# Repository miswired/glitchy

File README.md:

# CircuitBreakerGadget

## Project Overview
Designed as an introduction into hardware hacking, the Glitchy can do power glitching to alter program execution and power analysis for extracting secrets from chips. 
See the [wiki](https://github.com/miswired/glitchy/wiki) for setup instructions and guides to performing the labs with the kit.

## Install
This project is hosted in two repos. The board firmware and PCB is hosted here. Please see the following instructions for setting up the build enviroment and programming. [Arduino-Setup](https://github.com/miswired/glitchy/wiki/Guide-%E2%80%90-Arduino-Setup)   

**The web gui has be substatually upgradded by Philip Kopyscinski!**  
See the following repo for the files you need to put on the SD card.  
https://github.com/pkopysci/miswired-glitchy-vue-app

## Comming Features
* Scripting power analysis attack
* Configure wifi from a config file on sd card isntead of having to reprogram

## Release Notes
### 2.0.0
#### New Features
* Completely new web GUI!!!
* Adjustability of glitching parameters from web interface

### 1.1.0
#### New Features
* None

#### Bug Fixes
* Fixed loading bug for the web interface

#### Backlog

* Add configuration of the glitching settings to the web interface instead of needing to reflash the chip
* Add wifi configuration to a config.ini file on the SD card instead of needing to reflash the chip

## Project Setup
Install Arduino IDE V1. Please see the following wiki for a setup guide. [Arduino-Setup](https://github.com/miswired/glitchy/wiki/Guide-%E2%80%90-Arduino-Setup)  

## Colaborators
**Miswired**  
https://github.com/miswired  
PCB Board and firmware  
  
**Philip J Kopyscinski**  
https://github.com/pkopysci  
Web GUI

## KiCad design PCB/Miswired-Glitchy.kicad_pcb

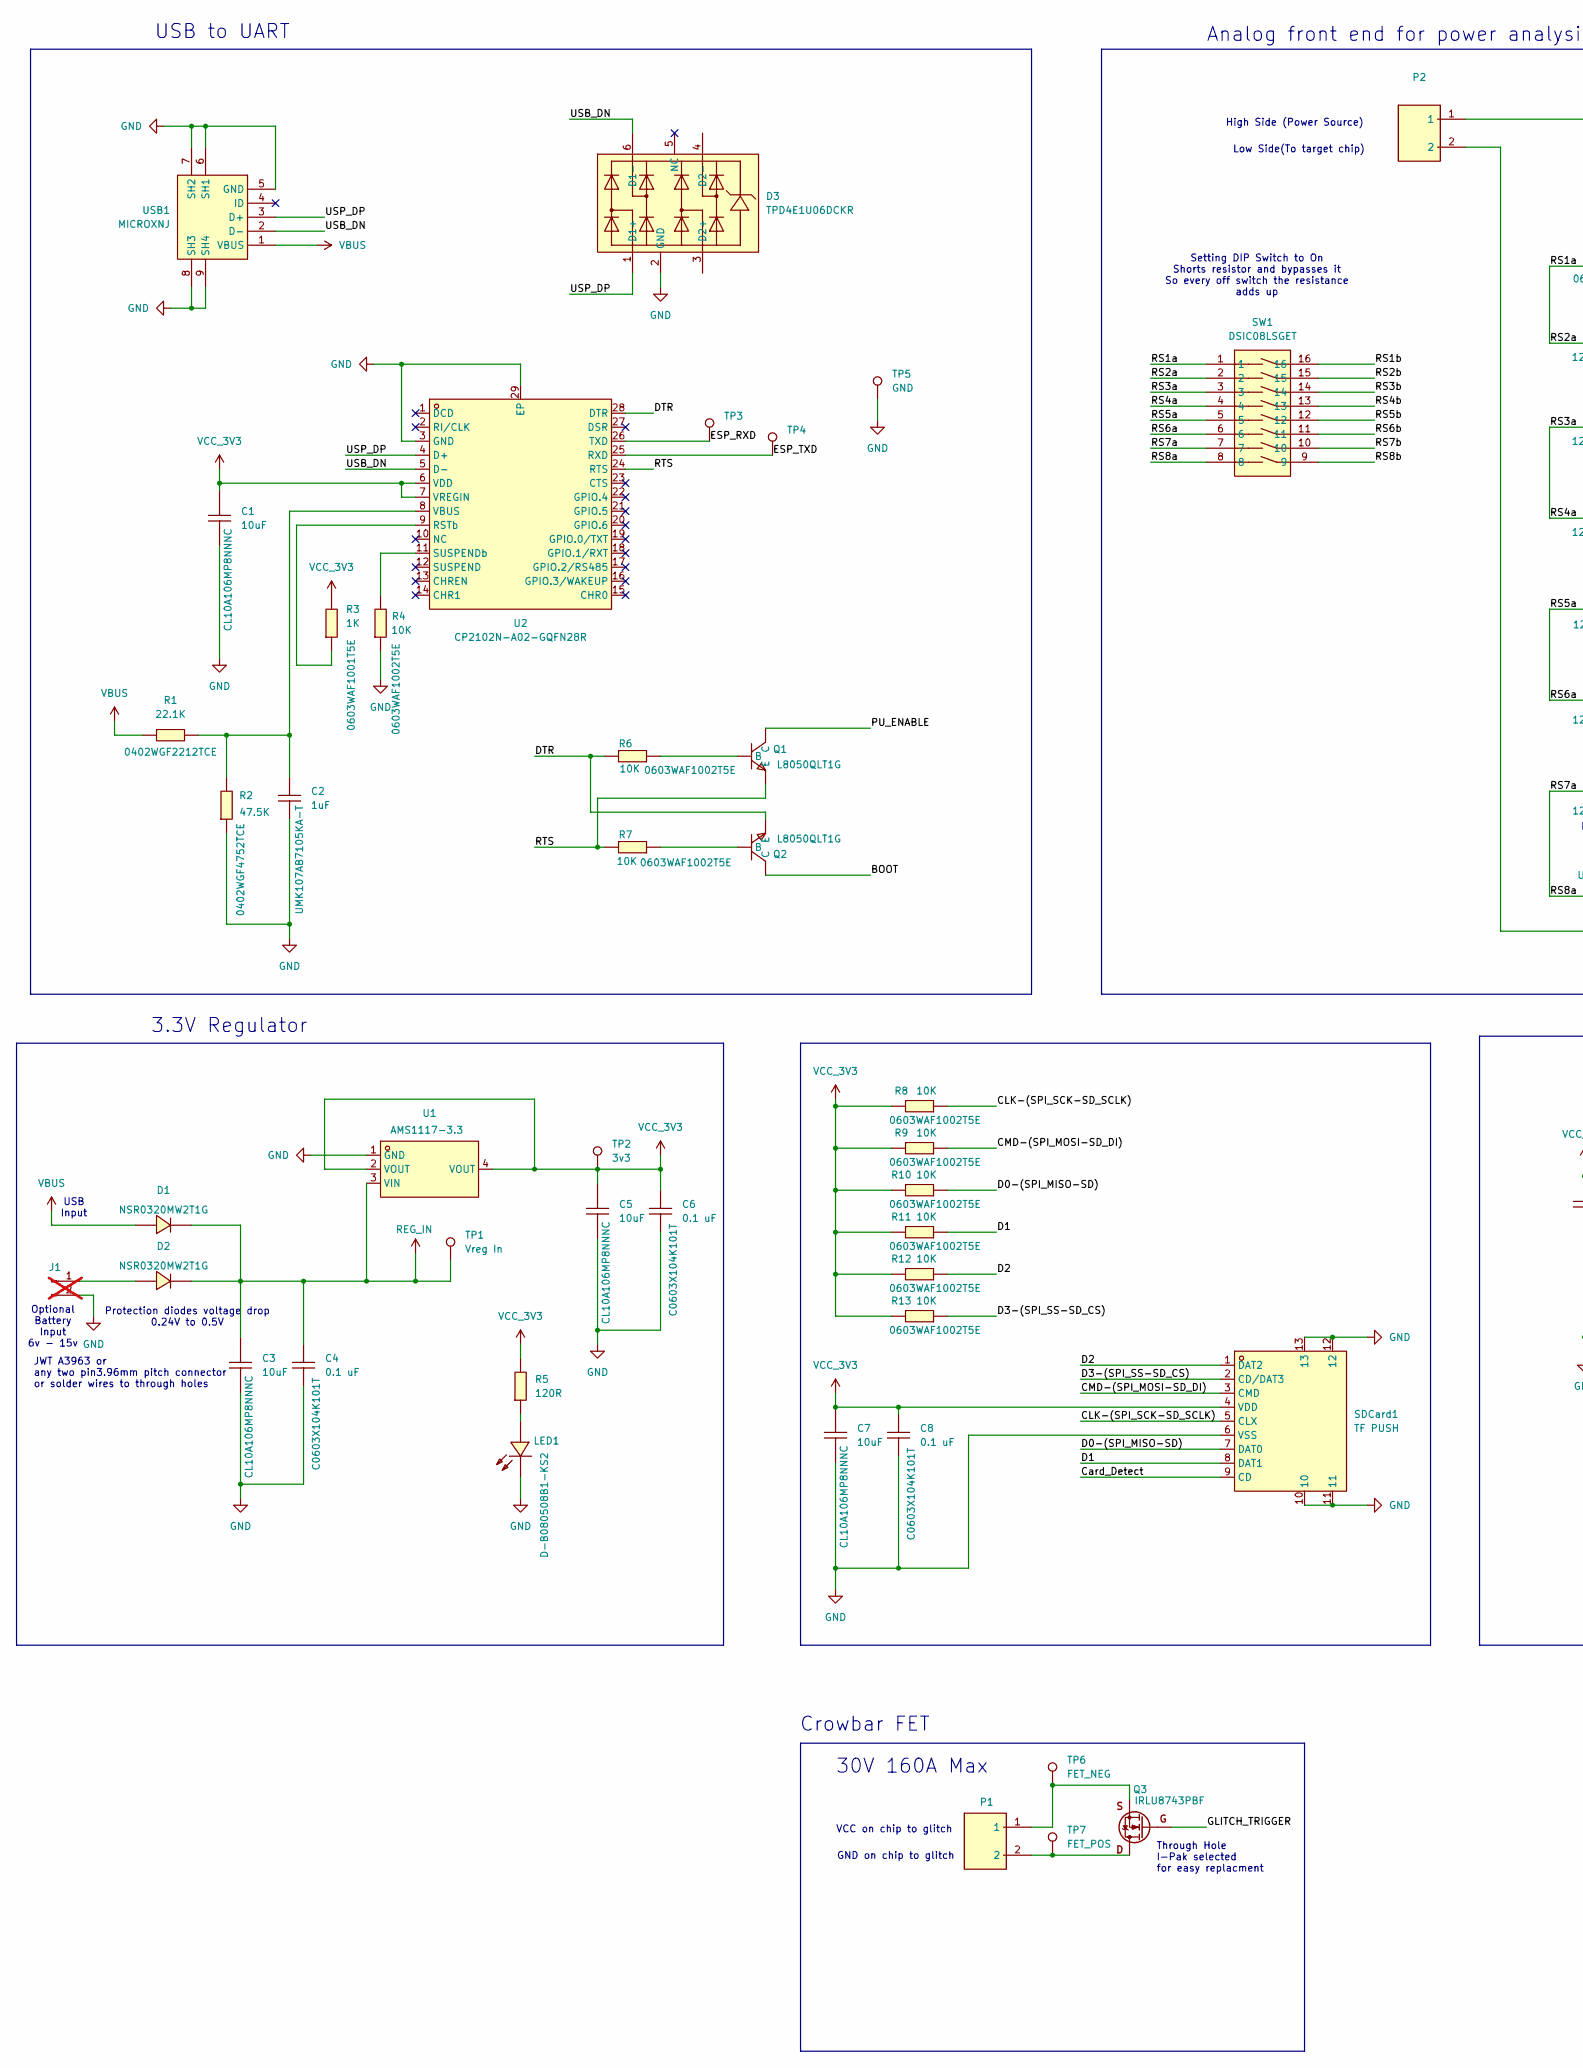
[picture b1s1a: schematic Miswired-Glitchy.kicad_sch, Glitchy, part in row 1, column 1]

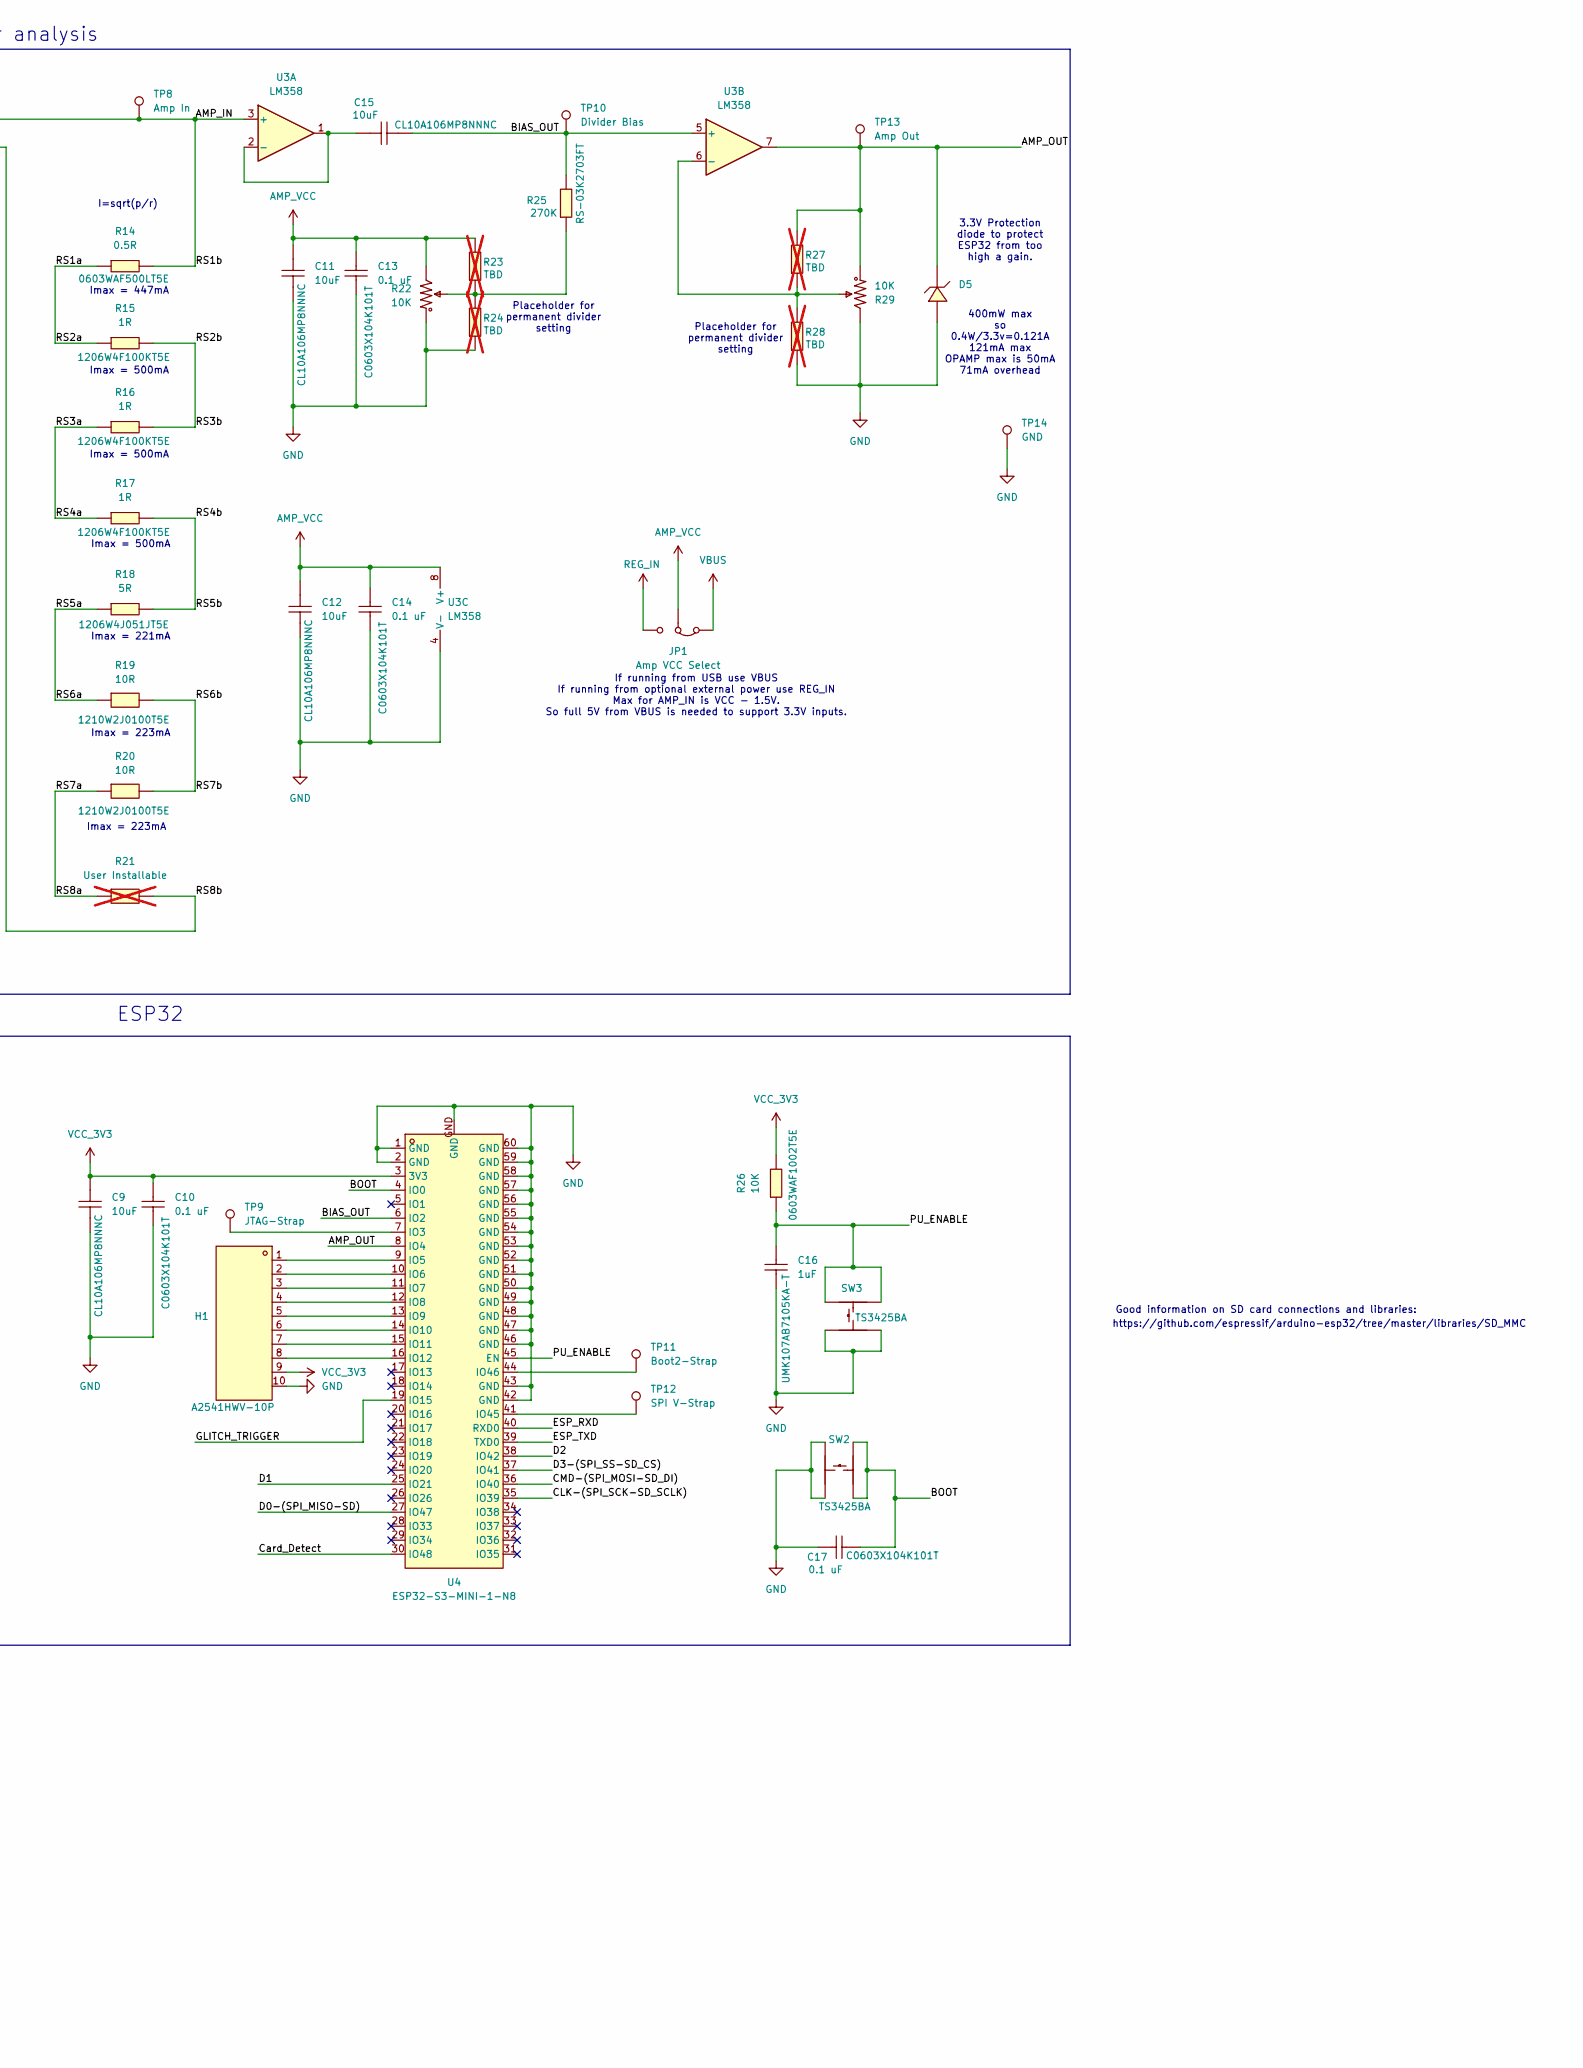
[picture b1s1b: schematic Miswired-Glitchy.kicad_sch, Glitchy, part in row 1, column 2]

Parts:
C1, C3, C5, C7, C9, C11, C12, C15: 10uF; C0603; MPN CL10A106MP8NNNC; LCSC Part C85713
C2, C16: 1uF; C0603; MPN UMK107AB7105KA-T; LCSC Part C105174
C4, C6, C8, C10, C13, C14, C17: 0.1 uF; C0603; MPN C0603X104K101T; LCSC Part C105907
D1, D2: SOD-323_L1.8-W1.3-LS2.5-RD; MPN NSR0320MW2T1G; LCSC Part C48192
D3: TPD4E1U06DCKR; SC-70-6_L2.2-W1.3-P0.65-LS2.1-BL; LCSC Part C194628
D5: PDZ3.3B,115; SOD-323_L1.7-W1.3-LS2.5-RD; MPN PDZ3.3B,115; LCSC Part C426855
H1: HDR-TH_10P-P2.54-V-F-1; MPN A2541HWV-10P; LCSC Part C225507
J1: Battery Placeholder; JWT_A3963_1x02_P3.96mm_Vertical; not fitted
JP1: Amp VCC Select; SolderJumper-3_P1.3mm_Bridged12_RoundedPad1.0x1.5mm_NumberL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
LED1: Blue; LED0805-RD; MPN D-B080508B1-KS2; LCSC Part C108412
P1, P2: CONN-TH_WJ126V-5.0-2P; MPN WJ126V-5.0-2P; LCSC Part C8404
Q1, Q2: SOT-23-3_L2.9-W1.3-P1.90-LS2.4-BR; MPN L8050QLT1G; LCSC Part C49581
Q3: IRLU8743PBF; TO-251-3_Vertical; MPN IRLU8743PBF
R1: 22.1K; R0402; MPN 0402WGF2212TCE; LCSC Part C43473
R2: 47.5K; R0402; MPN 0402WGF4752TCE; LCSC Part C25896
R3: 1K; R0603; MPN 0603WAF1001T5E; LCSC Part C21190
R4, R6, R7, R8, R9, R10, R11, R12, R13, R26: 10K; R0603; MPN 0603WAF1002T5E; LCSC Part C25804
R5: 120R; R0603; MPN 0603WAF1200T5E; LCSC Part C22787
R14: 0.5R; R0603; MPN 0603WAF500LT5E; LCSC Part C45312
R15, R16, R17: 1R; R1206; MPN 1206W4F100KT5E; LCSC Part C17928
R18: 5R; R1206; MPN 1206W4J051JT5E; LCSC Part C37912
R19, R20: 10R; R1210; MPN 1210W2J0100T5E; LCSC Part C473562
R21: User Installable; R_Box_L8.4mm_W2.5mm_P5.08mm; not fitted
R22, R29: 10K; RES-ADJ-TH_3P-L10.0-W10.0-P2.50-L; MPN 3296W-1-103; LCSC Part C118954
R23, R24, R27, R28: TBD; R0603; not fitted
R25: 270K; R0603; MPN RS-03K2703FT; LCSC Part C310276
SDCard1: TF PUSH; TF-SMD_TF-PUSH; LCSC Part C393941
SW1: DSIC08LSGET; SW-SMD_DSIC08LSGET; LCSC Part C54953
SW2, SW3: SW-SMD_4P-L4.2-W3.2-P2.15-LS4.6-1; MPN TS3425BA; LCSC Part C2681476
TP1: Vreg In; TestPoint_Pad_2.0x2.0mm
TP2: 3v3; TestPoint_Pad_2.0x2.0mm
TP3, TP4: TestPoint_Pad_2.0x2.0mm
TP5: GND; TestPoint_Pad_2.0x2.0mm
TP6: FET_NEG; TestPoint_THTPad_D2.0mm_Drill1.0mm
TP7: FET_POS; TestPoint_THTPad_D2.0mm_Drill1.0mm
TP8: Amp In; TestPoint_THTPad_D2.0mm_Drill1.0mm
TP9: JTAG-Strap; TestPoint_Pad_2.0x2.0mm
TP10: Divider Bias; TestPoint_THTPad_D2.0mm_Drill1.0mm
TP11: Boot2-Strap; TestPoint_Pad_2.0x2.0mm
TP12: SPI V-Strap; TestPoint_Pad_2.0x2.0mm
TP13: Amp Out; TestPoint_THTPad_D2.0mm_Drill1.0mm
TP14: GND; TestPoint_THTPad_D2.0mm_Drill1.0mm
U1: SOT-223-3_L6.5-W3.4-P2.30-LS7.0-BR; MPN AMS1117-3.3; LCSC Part C6186
U2: CP2102N-A02-GQFN28R; QFN-28_L5.0-W5.0-P0.50-TL-EP3.3; LCSC Part C964632
U3: LM358; SOP-8_L4.9-W3.9-P1.27-LS6.0-BL; MPN LM358DT; LCSC Part C9418
U4: ESP32-S3-MINI-1-N8; BULETM-SMD_ESP32-S3-MINI-1-N8; LCSC Part C2913206
USB1: MICROXNJ; MICRO-USB-SMD_MICROXNJ; LCSC Part C404969

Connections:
/AMP_IN: P2.1, R14.2, SW1.16, TP8.1, U3.3 (+)
/AMP_OUT: D5.1 (K), R27.2, R29.1, TP13.1, U3.7, U4.8 (IO4)
/BIAS_OUT: C15.2, R25.2, TP10.1, U3.5 (+), U4.6 (IO2)
/BOOT: C17.2, Q2.3 (C), SW2.1, SW2.2, U4.4 (IO0)
/CLK-(SPI_SCK-SD_SCLK): R8.1, SDCard1.5 (CLX), U4.35 (IO39)
/CMD-(SPI_MOSI-SD_DI): R9.1, SDCard1.3 (CMD), U4.36 (IO40)
/Card_Detect: SDCard1.9 (CD), U4.30 (IO48)
/D0-(SPI_MISO-SD): R10.1, SDCard1.7 (DAT0), U4.27 (IO47)
/D1: R11.1, SDCard1.8 (DAT1), U4.25 (IO21)
/D2: R12.1, SDCard1.1 (DAT2), U4.38 (IO42)
/D3-(SPI_SS-SD_CS): R13.1, SDCard1.2 (CD/DAT3), U4.37 (IO41)
/DTR: Q2.2 (E), R6.2, U2.28 (DTR)
/ESP_RXD: TP3.1, U2.26 (TXD), U4.40 (RXD0)
/ESP_TXD: TP4.1, U2.25 (RXD), U4.39 (TXD0)
/GLITCH_TRIGGER: Q3.1 (G), U4.19 (IO15)
/PU_ENABLE: C16.2, Q1.3 (C), R26.1, SW3.1, SW3.2, U4.45 (EN)
/RS1a: R14.1, R15.1, SW1.1, SW1.2
/RS2b: R15.2, R16.2, SW1.14, SW1.15
/RS3a: R16.1, R17.1, SW1.3, SW1.4
/RS4b: R17.2, R18.2, SW1.12, SW1.13
/RS5a: R18.1, R19.1, SW1.5, SW1.6
/RS6b: R19.2, R20.2, SW1.10, SW1.11
/RS7a: R20.1, R21.1, SW1.7, SW1.8
/RS8b: P2.2, R21.2, SW1.9
/RTS: Q1.2 (E), R7.2, U2.24 (RTS)
/USB_DN: D3.6 (D1-), U2.5 (D-), USB1.2 (D-)
/USP_DP: D3.1 (D1+), U2.4 (D+), USB1.3 (D+)
AMP_VCC: C11.1, C12.1, C13.2, C14.2, JP1.2 (C), R22.3, R23.2, U3.8 (V+)
GND: C1.2, C2.1, C3.2, C4.1, C5.2, C6.1, C7.2, C8.1, C9.2, C10.1, C11.2, C12.2, C13.1, C14.1, C16.1, C17.1, D3.2 (GND), D5.2 (A), H1.10, J1.2, LED1.1 (K), R2.1, R4.1, R22.1, R24.1, R28.1, R29.3, SDCard1.6 (VSS), SDCard1.10, SDCard1.11, SDCard1.12, SDCard1.13, SW2.3, SW2.4, SW3.3, SW3.4, TP5.1, TP14.1, U1.1 (GND), U2.3 (GND), U2.29 (EP), U3.4 (V-), U4.1 (GND), U4.2 (GND), U4.42 (GND), U4.43 (GND), U4.46 (GND), U4.47 (GND), U4.48 (GND), U4.49 (GND), U4.50 (GND), U4.51 (GND), U4.52 (GND), U4.53 (GND), U4.54 (GND), U4.55 (GND), U4.56 (GND), U4.57 (GND), U4.58 (GND), U4.59 (GND), U4.60 (GND), U4.GND, USB1.5 (GND), USB1.6 (SH1), USB1.7 (SH2), USB1.8 (SH3), USB1.9 (SH4)
unnamed: D2.2 (A), J1.1
unnamed: LED1.2 (A), R5.1
unnamed: Q1.1 (B), R6.1
unnamed: Q2.1 (B), R7.1
unnamed: P1.2, Q3.2 (D), TP7.1
unnamed: P1.1, Q3.3 (S), TP6.1
unnamed: R22.2, R23.1, R24.2, R25.1
unnamed: R3.1, U2.9 (RSTb)
unnamed: R4.2, U2.11 (SUSPENDb)
unnamed: C2.2, R1.2, R2.2, U2.8 (VBUS)
unnamed: C15.1, U3.1, U3.2 (-)
unnamed: R27.1, R28.2, R29.2, U3.6 (-)
unnamed: TP9.1, U4.7 (IO3)
unnamed: H1.1, U4.9 (IO5)
unnamed: H1.2, U4.10 (IO6)
unnamed: H1.3, U4.11 (IO7)
unnamed: H1.4, U4.12 (IO8)
unnamed: H1.5, U4.13 (IO9)
unnamed: H1.6, U4.14 (IO10)
unnamed: H1.7, U4.15 (IO11)
unnamed: H1.8, U4.16 (IO12)
unnamed: TP12.1, U4.41 (IO45)
unnamed: TP11.1, U4.44 (IO46)
REG_IN: C3.1, C4.2, D1.1 (C), D2.1 (C), JP1.3 (B), TP1.1, U1.3 (VIN)
VBUS: D1.2 (A), JP1.1 (A), R1.1, USB1.1 (VBUS)
VCC_3V3: C1.1, C5.1, C6.2, C7.1, C8.2, C9.1, C10.2, H1.9, R3.2, R5.2, R8.2, R9.2, R10.2, R11.2, R12.2, R13.2, R26.2, SDCard1.4 (VDD), TP2.1, U1.2 (VOUT), U1.4 (VOUT), U2.6 (VDD), U2.7 (VREGIN), U4.3 (3V3)

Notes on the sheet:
Good information on SD card connections and libraries:
400mW max so 0.4W/3.3v=0.121A 121mA max OPAMP max is 50mA 71mA overhead
Placeholder for permanent divider setting
High Side (Power Source)
If running from USB use VBUS If running from optional external power use REG_IN Max for AMP_IN is VCC - 1.5V. So full 5V from VBUS is needed to support 3.3V inputs.
Imax = 500mA
https://github.com/espressif/arduino-esp32/tree/master/libraries/SD_MMC
Crowbar FET
Imax = 223mA
Low Side(To target chip)
3.3V Regulator
GND on chip to glitch
Optional Battery Input 6v - 15v
ESP32
Imax = 221mA
Setting DIP Switch to On Shorts resistor and bypasses it So every off switch the resistance adds up
I=sqrt(p/r)
Through Hole I-Pak selected for easy replacment
VCC on chip to glitch
3.3V Protection diode to protect ESP32 from too high a gain.
30V 160A Max
USB to UART
JWT A3963 or any two pin3.96mm pitch connector or solder wires to through holes
Imax = 447mA
Protection diodes voltage drop 0.24V to 0.5V
Analog front end for power analysis
USB Input

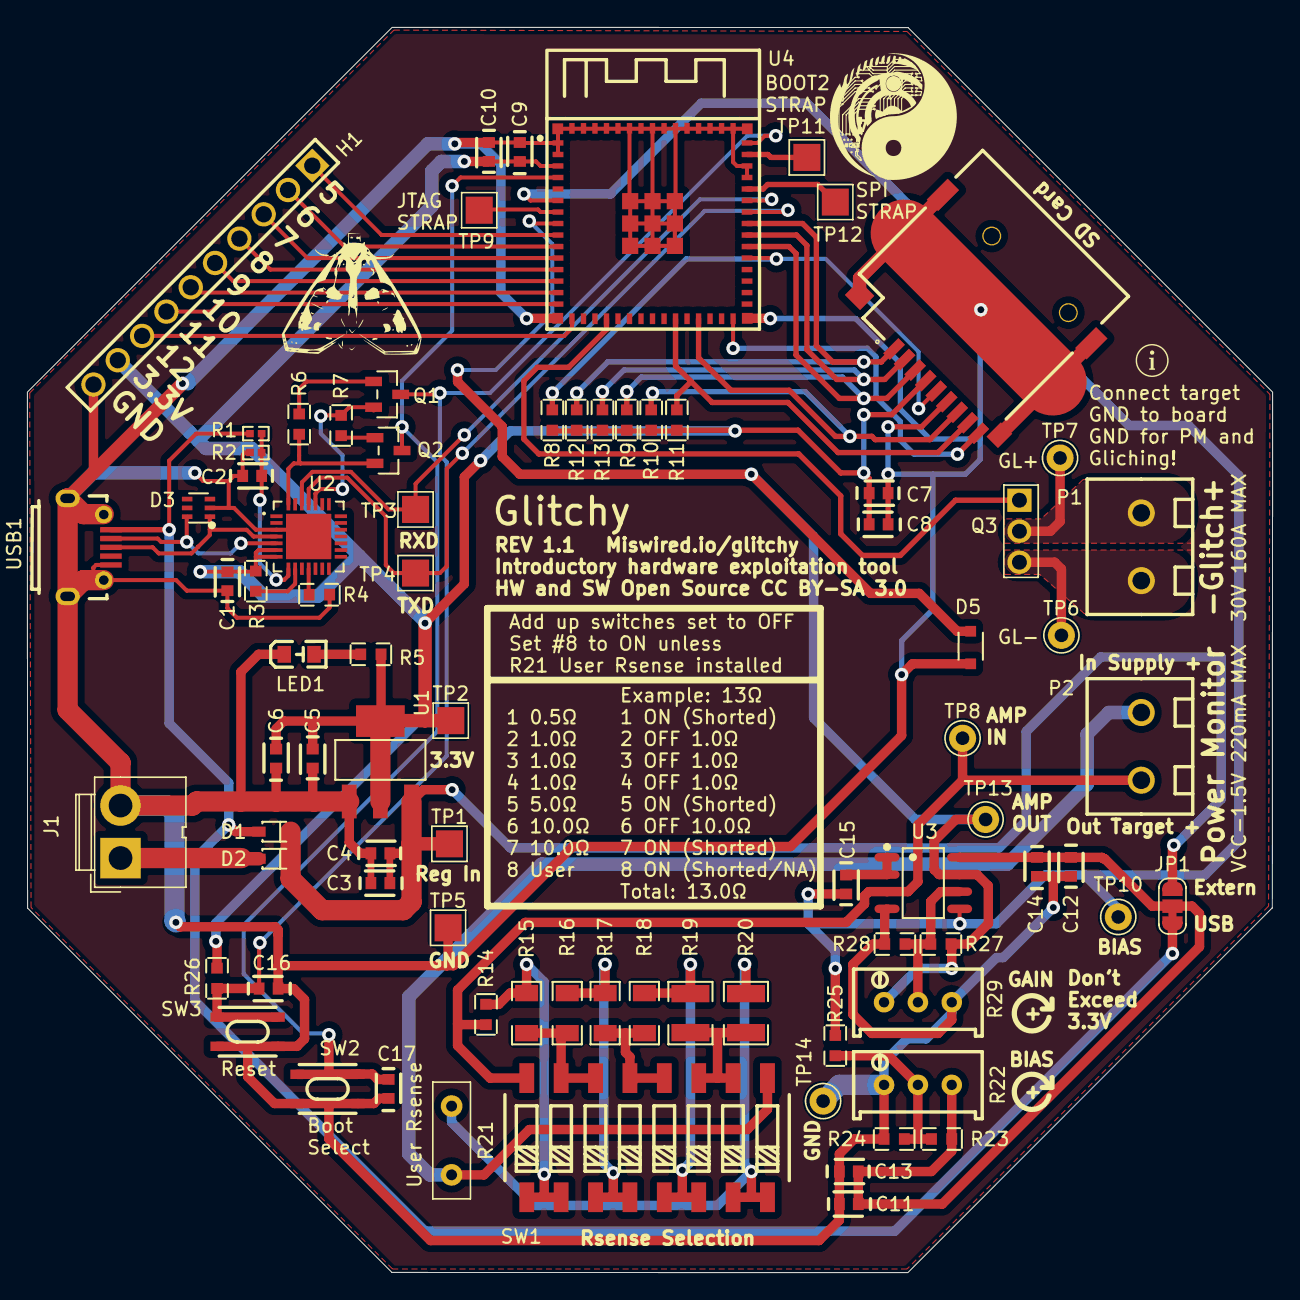
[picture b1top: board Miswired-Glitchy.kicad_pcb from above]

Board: 2 copper layers, 92.0 x 92.0 mm, 82 parts (0 on the bottom side), 55 nets.

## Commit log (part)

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2024-07-29 Initial Commit
    Current state of project, PCB REV1.1 ordered, untested. Code is a collection of small hardware tests. Project not yet complete.
2024-07-29 Adding branch for the Project Circuit Breaker
    Adding branch for the Project Circuit Breaker version of the PCB. This is really just some silkscreen changes to the PCB for looks and branding. Still a work in progress, not yet delivered.
2024-07-29 Updating some renders and docs
    Accidently had the project circuit breaker docs in here
2024-08-02 Lots of test code added
    The glitchy-tabs-test is the latest featured test code.
2024-08-03 Sending values automatically with timer
2024-08-03 Added circular buffer and continuous reading to chart
2024-08-04 Made a new project, got streaming plugin working
2024-08-04 Got toggle working
2024-08-05 Power Analysis good, glitching slow again
2024-08-05 latest tests to try and fix the glitch times not working
2024-08-05 glitch timing is working manuallygit config user.name miswired!
2024-08-06 new project trying spi module, basic test working
2024-08-07 The Gliching and Power both workgit status! Code needs cleaned up
2024-08-08 Right before cleaning up for release
2024-08-08 Cleaning up and adding docs
2024-08-08 Lots of changes to try and fix reload bug
2024-08-08 Removed old code in repo
2024-08-08 WTF, git ignore fail
2024-08-09 Trying to fix reload issue
    The reload hangs don't seem to be an issue but getting some warnings that I still need to fix.
2024-08-12 Tried changing encoding thinking that it may be causing misinterpretation of the js file
2024-08-12 Changed order of imports
    Seems to help the page load much better. Still getting some retrieve failures for chartjs streaming plugin for some reason. But reloads appear to be much more reliable.
2024-08-12 Fixed CSS parsing warning
    Drop shadow on button apparently had a syntax error.
2024-08-18 Changing the welcome message to remove bug notification
2024-09-09 Added glitch tuning params
2024-09-23 Removing web gui for external repo
    https://github.com/pkopysci/miswired-glitchy-vue-app
2024-12-25 Cleanup and start of dev branch
2024-12-25 more cleanup
2025-01-14 Moving over some branding
2025-01-14 Adjusting silkscreen
2025-02-18 Final version submitted
2025-03-19 Major Refactor, moved to platform IO
    In order to fix the page loading I had to use a whole different IDE, libraries, and port everything over to PlatformIO. It works way better now.
2025-03-19 Code Ported to PlatformIO
    Major refactor of code. Had to port everything over to PlatformIO and new libraries in order to fix the web loading bug. It's working much better now.

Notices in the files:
PCB/Miswired-Glitchy.kicad_pcb:
HW and SW Open Source CC BY-SA 3.0
